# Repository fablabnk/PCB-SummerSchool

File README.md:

This is a repo to support our [_Printed Circuit Board (PCB) Design Summer School_](https://luma.com/ke7vlmk2) series of events 

- Please join the Discord server [here](https://discord.gg/XeFhvPQ43z) to share tips and info

# The Basics

​Join us for Maker Summer School! In this summer series, you can learn how to design your own printed circuit board using the free open source (FOSS) software package KiCad.

- ​Over four evening sessions, we'll take you on a gentle dive into the typically hidden-world of everyday electronics and help you start to make your own.
- All sessions takes place from 18:30 in the 42 auditorium
- The first session is a general intro to the topic, to see if it's your thing
- If you like it join the "learning pact" for the next 3 weeks to design and send for your own board
- The best finished boards will be sponsored by the school

From LED 'blinky' badges to, mini-keyboards and games-consoles, circuit-board jewelry and synthesisers - we'll take a look at a series of example projects that we’ve produced over the last year and use those as jumping-off points for your own designs. So whether you're a budding hardware engineer or an artist looking explore a new fabrication technique - you'll find the practical tools you need here.

​And of course we’ll learn some electronics too as a side effect :)

# Inspirational Projects

See the list [here](./INSPIRATIONAL_PROJECTS.md) - including FabLab members projects!

# 17.06 [Session 1: The Printed Circuit Design Workflow](https://github.com/fablabnk/PCB-SummerSchool/blob/main/SESSION1.md)
- Trip to China: Virtual tour of a PCB factory and JLCPCB
- Anatomy of a Printed Circuit Board
- ​“Hello Hardware World”: Laying out, checking and uploading a blinky badge using KiCad
- ​Components and Their Footprints: through-hole vs surface mount
- ​Choose your own project for the coming weeks

# 24.06 Session 2: Deeper-Dive into Schematics and Boards
- How to create a schematic (and re-use those of others)
- ​Performing an electrical rules check (ERC)
- ​From schematic to board: board shape, footprints and layouts (DRC)
- ​Assisted individual project time

# 01.07 Session 3: Individual Projects and Advanced Topics
- Traces vs pours and other routing tips-and-tricks
- ​"Round-tripping" for artistic PCB design: from KiCad to Inkscape and back
- ​Case study: Designing to mill-it-yourself (MIY) on our CNC mill
- ​How to make your own custom symbol and footprints
- ​Assisted individual project time

# 08.07 Session 4: Advanced Topics and Ordering
- Big push to complete and order your designs!
- ​Design options: beyond 2-layer boards and rigid PCBs
- ​Case study: Fully-assembled PCBs (e.g. butterfly project)
- ​Fabrication with JLCPCB: tips and tricks

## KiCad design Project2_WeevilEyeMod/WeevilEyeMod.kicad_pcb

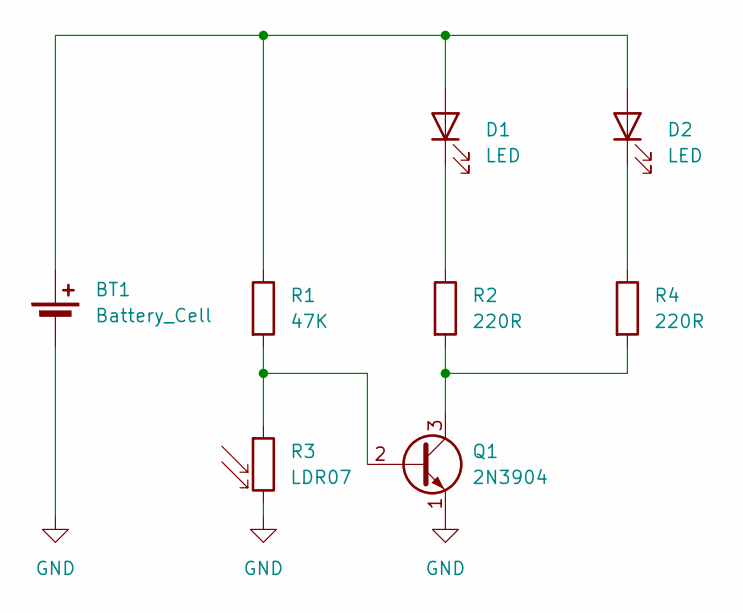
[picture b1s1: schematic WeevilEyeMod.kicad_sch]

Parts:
BT1: Battery_Cell; BatteryHolder_ComfortableElectronic_CH273-2450_1x2450
D1, D2: LED; LED_D5.0mm
Q1: 2N3904; TO-92_Inline_Wide
R1: 47K; R_Axial_DIN0204_L3.6mm_D1.6mm_P7.62mm_Horizontal
R2, R4: 220R; R_Axial_DIN0204_L3.6mm_D1.6mm_P7.62mm_Horizontal
R3: LDR07; R_LDR_5.1x4.3mm_P3.4mm_Vertical

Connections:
GND: BT1.2 (-), Q1.1 (E), R3.2
unnamed: BT1.1 (+), D1.2 (A), D2.2 (A), R1.1
unnamed: D1.1 (K), R2.1
unnamed: D2.1 (K), R4.1
unnamed: Q1.2 (B), R1.2, R3.1
unnamed: Q1.3 (C), R2.2, R4.2

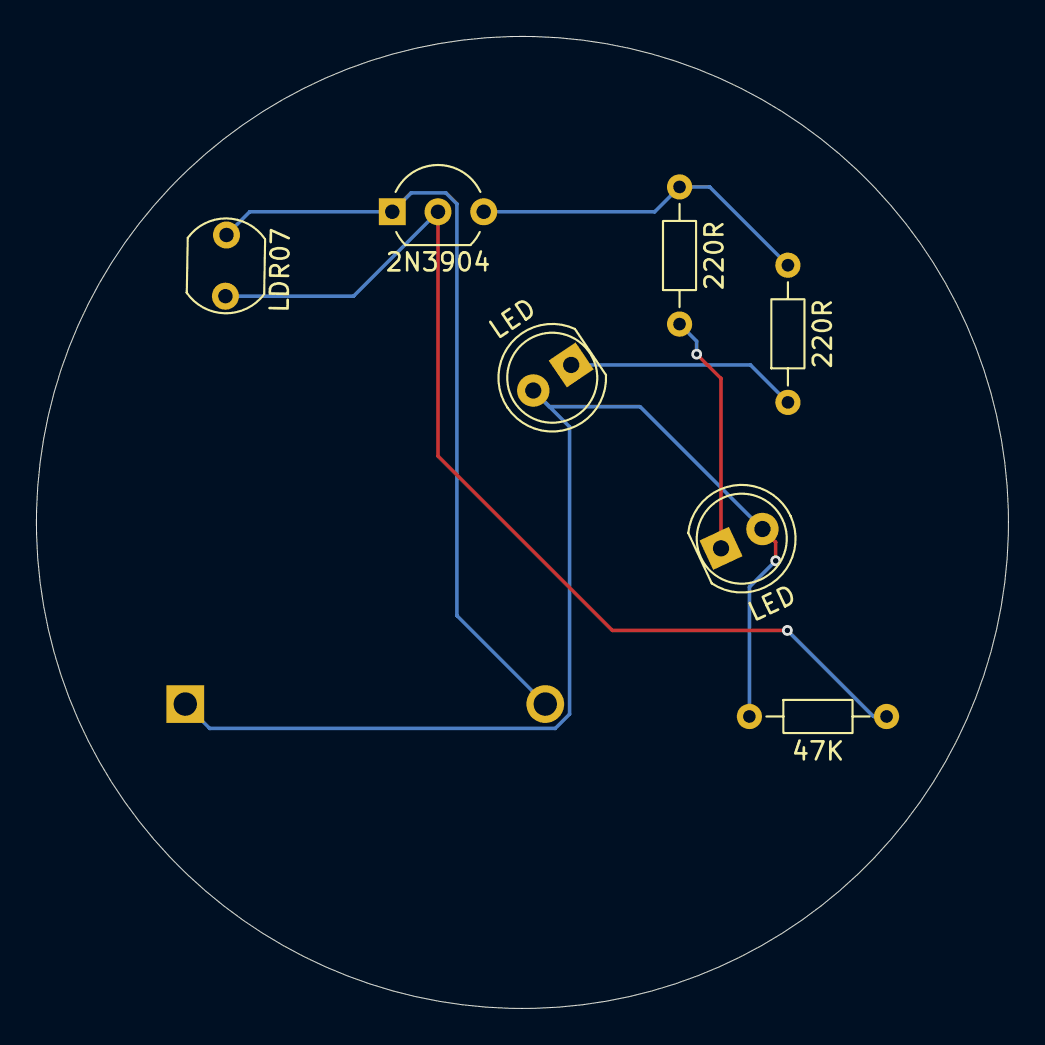
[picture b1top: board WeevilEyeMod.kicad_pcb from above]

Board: 2 copper layers, 54.0 x 54.0 mm, 8 parts (1 on the bottom side), 6 nets.

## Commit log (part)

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2025-09-16 adding docs and resources for session 2
2025-09-17 updating session 2 docs
2025-09-24 updating before session 3
2025-10-01 adding SESSION.md
2025-10-01 adding SESSION4 materials
2025-10-01 updated discord link
2026-06-17 Updating for 2026
2026-06-17 Fix session title link format in README
    Updated the session title link format in the README.
2026-06-17 Fix grammar in session details of README
2026-06-24 Updated notes and examples for Session 2
2026-06-30 Updating plan for Session 3
